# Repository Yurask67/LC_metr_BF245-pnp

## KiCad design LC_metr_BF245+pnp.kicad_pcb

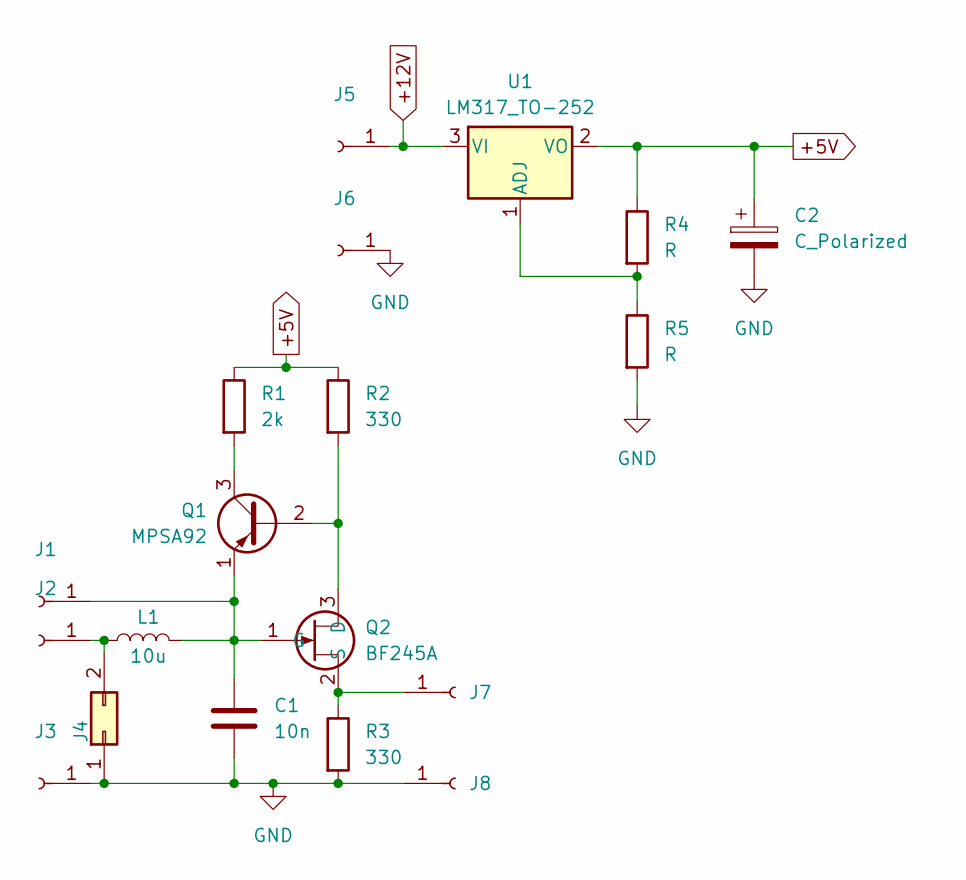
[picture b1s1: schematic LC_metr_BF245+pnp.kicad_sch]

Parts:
C1: 10n; C_Disc_D9.0mm_W5.0mm_P5.00mm
C2: C_Polarized; C_Radial_D6.3mm_H7.0mm_P2.50mm
J1, J2, J3, J5, J6, J7, J8: Conn_01x01_Socket; Pin_3mm_Dril_1mm
J4: Conn_02x01; PinSocket_2x01_P2.54mm_Vertical
L1: 10u; L_Axial_L17.5mm_D12.0mm_P20.32mm_Horizontal_Vishay_IM-10-46
Q1: MPSA92; TO-92_Inline
Q2: BF245A; TO-92_Inline
R1: 2k; R_Axial_DIN0207_L6.3mm_D2.5mm_P10.16mm_Horizontal
R2, R3: 330; R_Axial_DIN0207_L6.3mm_D2.5mm_P10.16mm_Horizontal
R4, R5: R; R_0805_2012Metric
U1: LM317_TO-252; TO-252-2

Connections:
+5V: C2.1, R1.1, R2.1, R4.1, U1.2 (VO)
+12V: J5.1, U1.3 (VI)
GND: C1.2, C2.2, J3.1, J4.1, J6.1, J8.1, R3.2, R5.2
unnamed: C1.1, J1.1, L1.2, Q1.1 (E), Q2.1 (G)
unnamed: J2.1, J4.2, L1.1
unnamed: J7.1, Q2.2 (S), R3.1
unnamed: Q1.2 (B), Q2.3 (D), R2.2
unnamed: Q1.3 (C), R1.2
unnamed: R4.2, R5.1, U1.1 (ADJ)

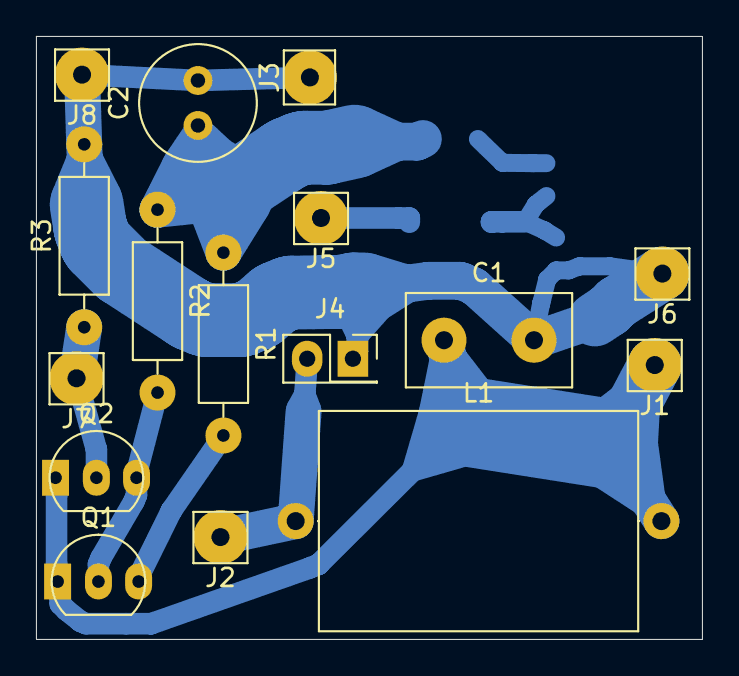
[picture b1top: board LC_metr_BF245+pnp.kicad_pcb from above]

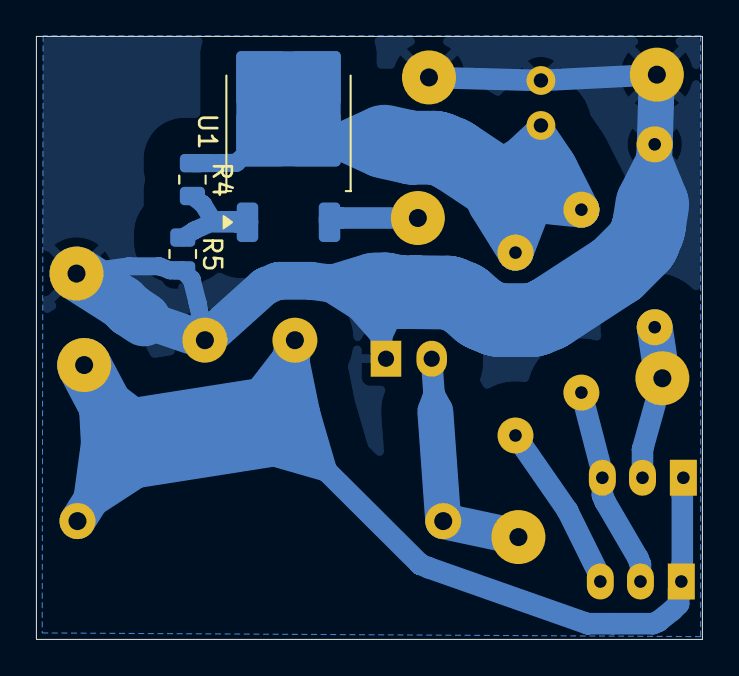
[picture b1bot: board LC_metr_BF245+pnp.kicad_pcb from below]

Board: 2 copper layers, 37.0 x 33.5 mm, 19 parts (3 on the bottom side), 9 nets.

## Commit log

2025-11-19 init
2025-11-19 оптимизация и доработка
    добавлены выходные клемы, оптимизированно размещение элементов топором
2025-11-20 оптимизация
    увеличена ширина проводников до 5 мм
2025-11-20 полигоны
    найден баг с зазорами полигонов, нужно цепян назначит созданный левый класс,
    если оставлять Default то берутся зазоры для полигона из класса цепей и не меняются настройками полигона
